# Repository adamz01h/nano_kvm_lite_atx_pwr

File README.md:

# nano_kvm_lite_atx_pwr
NanoKVM ATX PWR Breakout
This code is under non commercial license use.
Private use only.

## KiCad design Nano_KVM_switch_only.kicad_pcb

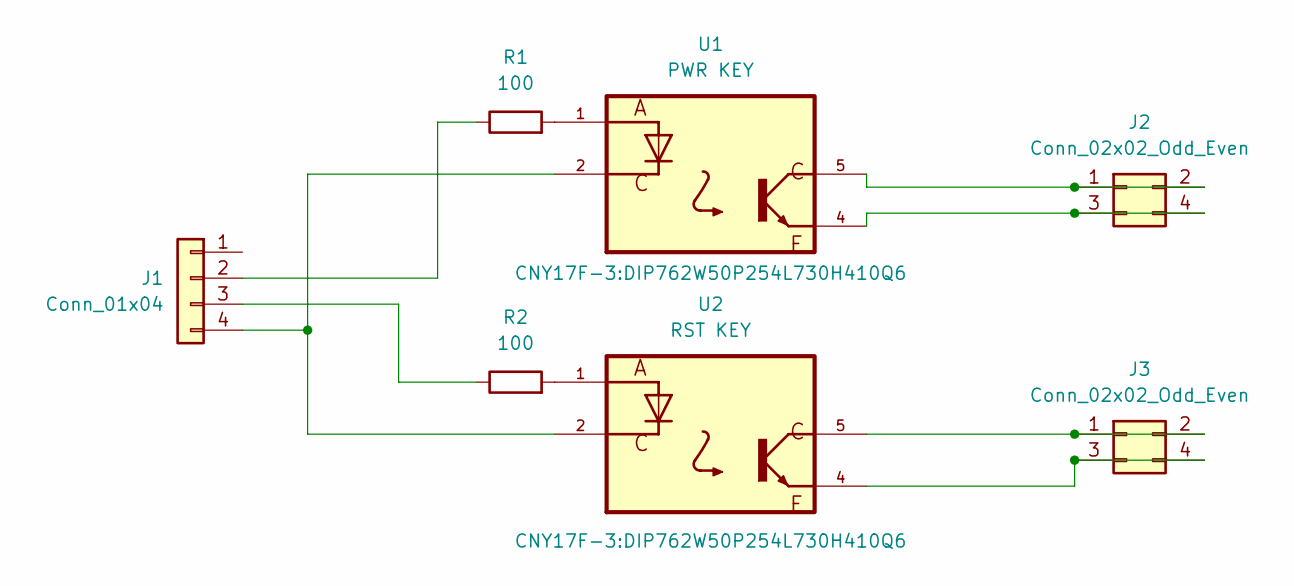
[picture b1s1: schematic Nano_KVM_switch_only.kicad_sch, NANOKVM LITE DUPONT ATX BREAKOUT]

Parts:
J1: Conn_01x04; PinHeader_1x04_P2.54mm_Vertical
J2, J3: Conn_02x02_Odd_Even; PinHeader_2x02_P2.54mm_Vertical
R1, R2: 100; R_Axial_DIN0207_L6.3mm_D2.5mm_P10.16mm_Horizontal
U1: PWR KEY; DIP762W50P254L730H410Q6
U2: RST KEY; DIP762W50P254L730H410Q6

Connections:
unnamed: J1.2, R1.1
unnamed: J1.3, R2.1
unnamed: J1.4, U1.2, U2.2
unnamed: J2.1, J2.2, U1.5
unnamed: J2.3, J2.4, U1.4
unnamed: J3.1, J3.2, U2.5
unnamed: J3.3, J3.4, U2.4
unnamed: R1.2, U1.1
unnamed: R2.2, U2.1

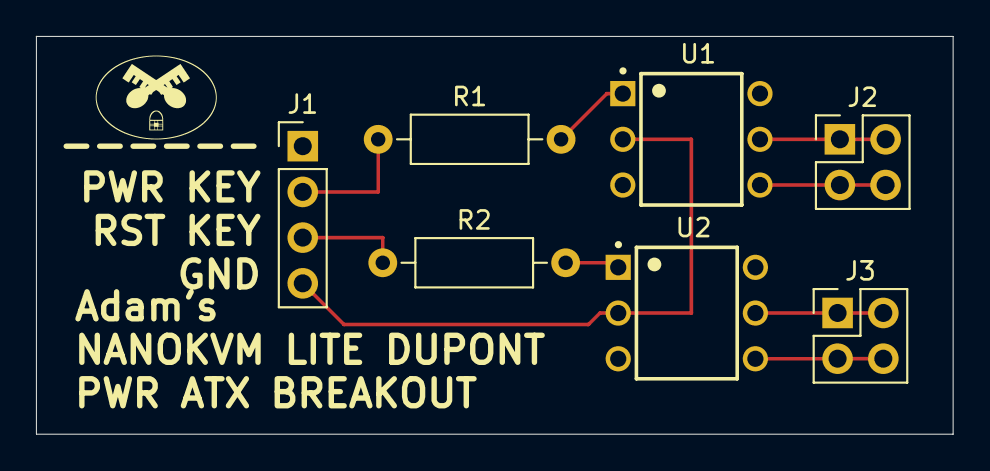
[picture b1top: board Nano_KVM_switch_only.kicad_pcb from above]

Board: 2 copper layers, 50.9 x 22.1 mm, 7 parts (0 on the bottom side), 9 nets.

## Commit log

2025-01-04 Update README.md
    Usage rights
2025-01-04 added pdf
2025-01-30 Added nanokvm pinouts
